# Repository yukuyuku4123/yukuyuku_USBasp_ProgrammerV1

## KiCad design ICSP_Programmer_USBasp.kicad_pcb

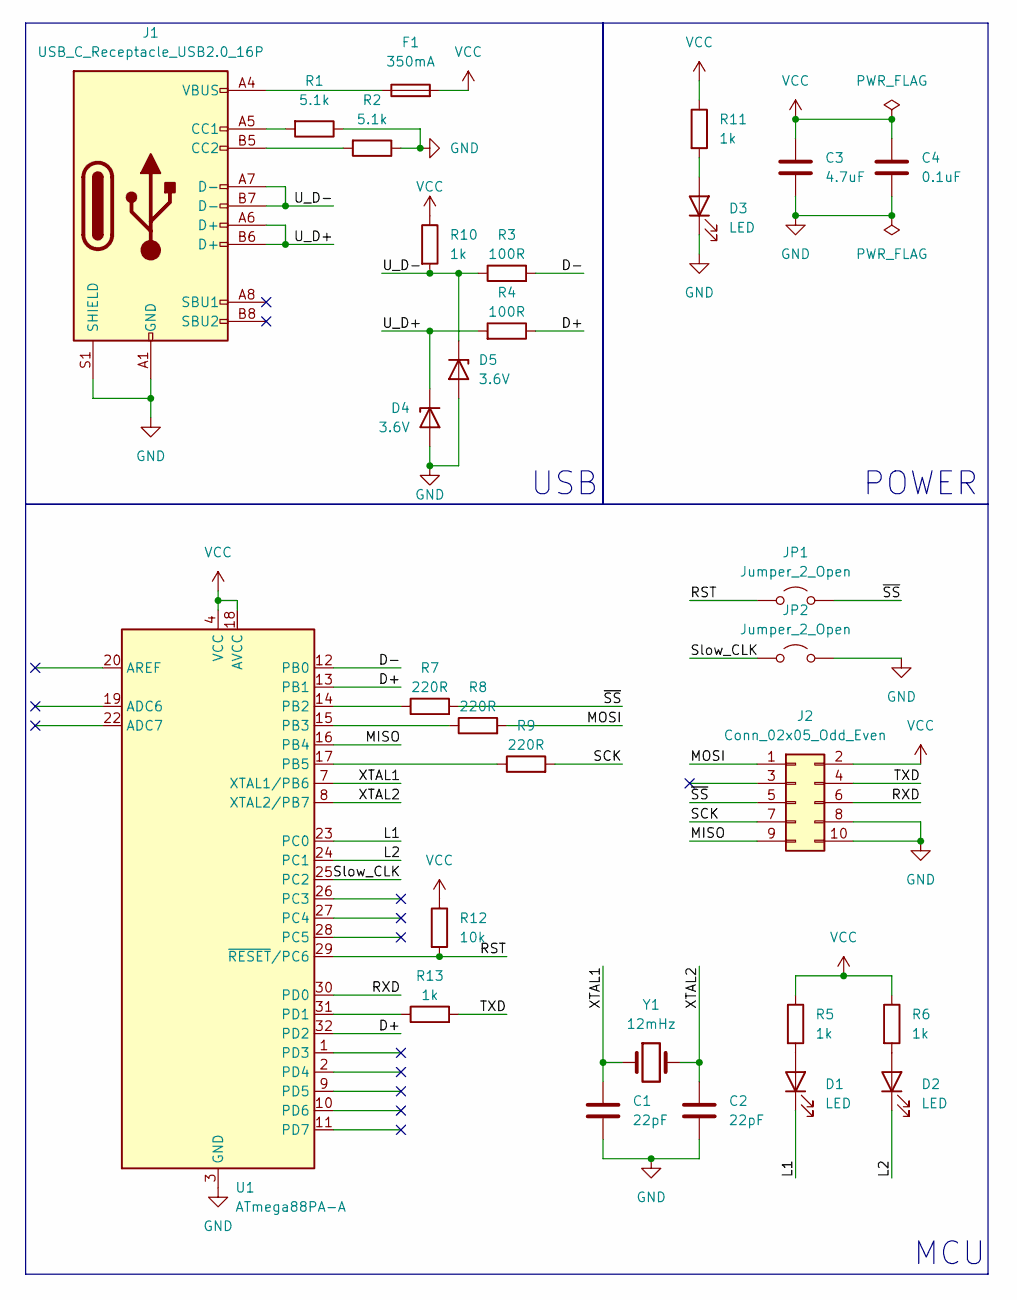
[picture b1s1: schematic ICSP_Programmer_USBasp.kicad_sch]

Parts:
C1, C2: 22pF; C_0402_1005Metric
C3: 4.7uF; C_0603_1608Metric
C4: 0.1uF; C_0402_1005Metric
D1, D2, D3: LED; LED_0603_1608Metric
D4, D5: 3.6V; D_SOD-323F
F1: 350mA; Fuse_0402_1005Metric
J1: USB_C_Receptacle_USB2.0_16P; USB_C_Receptacle_GCT_USB4105-xx-A_16P_TopMnt_Horizontal
J2: Conn_02x05_Odd_Even; PinHeader_2x05_P2.54mm_Vertical
JP1, JP2: Jumper_2_Open; PinHeader_1x02_P2.54mm_Vertical
R1, R2: 5.1k; R_0603_1608Metric
R3, R4: 100R; R_0603_1608Metric
R5, R6, R10, R11, R13: 1k; R_0603_1608Metric
R7, R8, R9: 220R; R_0603_1608Metric
R12: 10k; R_0603_1608Metric
U1: ATmega88PA-A; TQFP-32_7x7mm_P0.8mm
Y1: 12mHz; Crystal_HC49-4H_Vertical

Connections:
/D+: R4.1, U1.13 (PB1), U1.32 (PD2)
/D-: R3.2, U1.12 (PB0)
/L1: D1.1 (K), U1.23 (PC0)
/L2: D2.1 (K), U1.24 (PC1)
/MISO: J2.9, U1.16 (PB4)
/MOSI: J2.1, R8.2
/RST: JP1.1 (A), R12.2, U1.29 (~RESET/PC6)
/RXD: J2.6, U1.30 (PD0)
/SCK: J2.7, R9.2
/Slow_CLK: JP2.1 (A), U1.25 (PC2)
/TXD: J2.4, R13.2
/U_D+: D4.1 (K), J1.A6 (D+), J1.B6 (D+), R4.2
/U_D-: D5.1 (K), J1.A7 (D-), J1.B7 (D-), R3.1, R10.2
/XTAL1: C1.1, U1.7 (XTAL1/PB6), Y1.1
/XTAL2: C2.1, U1.8 (XTAL2/PB7), Y1.2
/~SS: J2.5, JP1.2 (B), R7.2
GND: C1.2, C2.2, C3.2, C4.2, D3.1 (K), D4.2 (A), D5.2 (A), J1.A1 (GND), J1.A12 (GND), J1.B1 (GND), J1.B12 (GND), J1.S1 (SHIELD), J2.8, J2.10, JP2.2 (B), R1.1, R2.1, U1.3 (GND), U1.5 (GND), U1.21 (GND)
unnamed: D1.2 (A), R5.2
unnamed: D2.2 (A), R6.2
unnamed: D3.2 (A), R11.2
unnamed: F1.1, J1.A4 (VBUS), J1.A9 (VBUS), J1.B4 (VBUS), J1.B9 (VBUS)
unnamed: J1.A5 (CC1), R1.2
unnamed: J1.B5 (CC2), R2.2
unnamed: R7.1, U1.14 (PB2)
unnamed: R8.1, U1.15 (PB3)
unnamed: R9.1, U1.17 (PB5)
unnamed: R13.1, U1.31 (PD1)
VCC: C3.1, C4.1, F1.2, J2.2, R5.1, R6.1, R10.1, R11.1, R12.1, U1.4 (VCC), U1.6 (VCC), U1.18 (AVCC)

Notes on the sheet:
USB
POWER
MCU

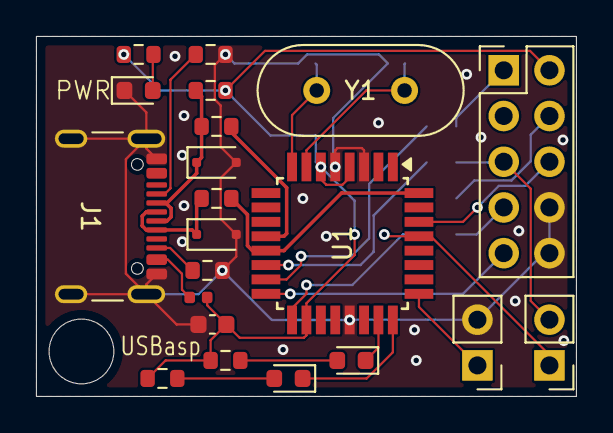
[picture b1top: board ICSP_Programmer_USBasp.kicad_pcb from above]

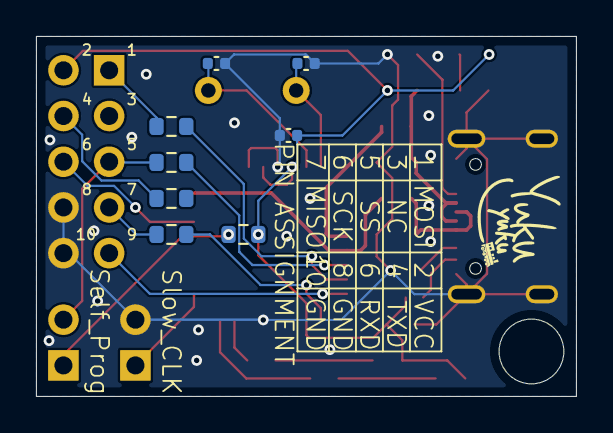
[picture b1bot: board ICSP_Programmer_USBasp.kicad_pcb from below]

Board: 2 copper layers, 30.0 x 20.0 mm, 29 parts (8 on the bottom side), 28 nets.

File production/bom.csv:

Designator,Footprint,Quantity,Value,LCSC Part #
"C1, C2",0402,2,22pF,
C3,0603,1,4.7uF,
C4,0402,1,0.1uF,
"D1, D2, D3",0603,3,LED,
"D4, D5",D_SOD-323F,2,3.6V,
F1,0402,1,350mA,
J1,USB_C_Receptacle_GCT_USB4105-xx-A_16P_TopMnt_Horizontal,1,USB_C_Receptacle_USB2.0_16P,
J2,PinHeader_2x05_P2.54mm_Vertical,1,Conn_02x05_Odd_Even,
"JP1, JP2",PinHeader_1x02_P2.54mm_Vertical,2,Jumper_2_Open,
"R1, R2",0603,2,5.1k,
"R10, R11, R13, R5, R6",0603,5,1k,
R12,0603,1,10k,
"R3, R4",0603,2,100R,
"R7, R8, R9",0603,3,220R,
U1,TQFP-32_7x7mm_P0.8mm,1,ATmega88PA-A,
Y1,Crystal_HC49-4H_Vertical,1,12mHz,

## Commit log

2024-07-27 Ver-1.0
